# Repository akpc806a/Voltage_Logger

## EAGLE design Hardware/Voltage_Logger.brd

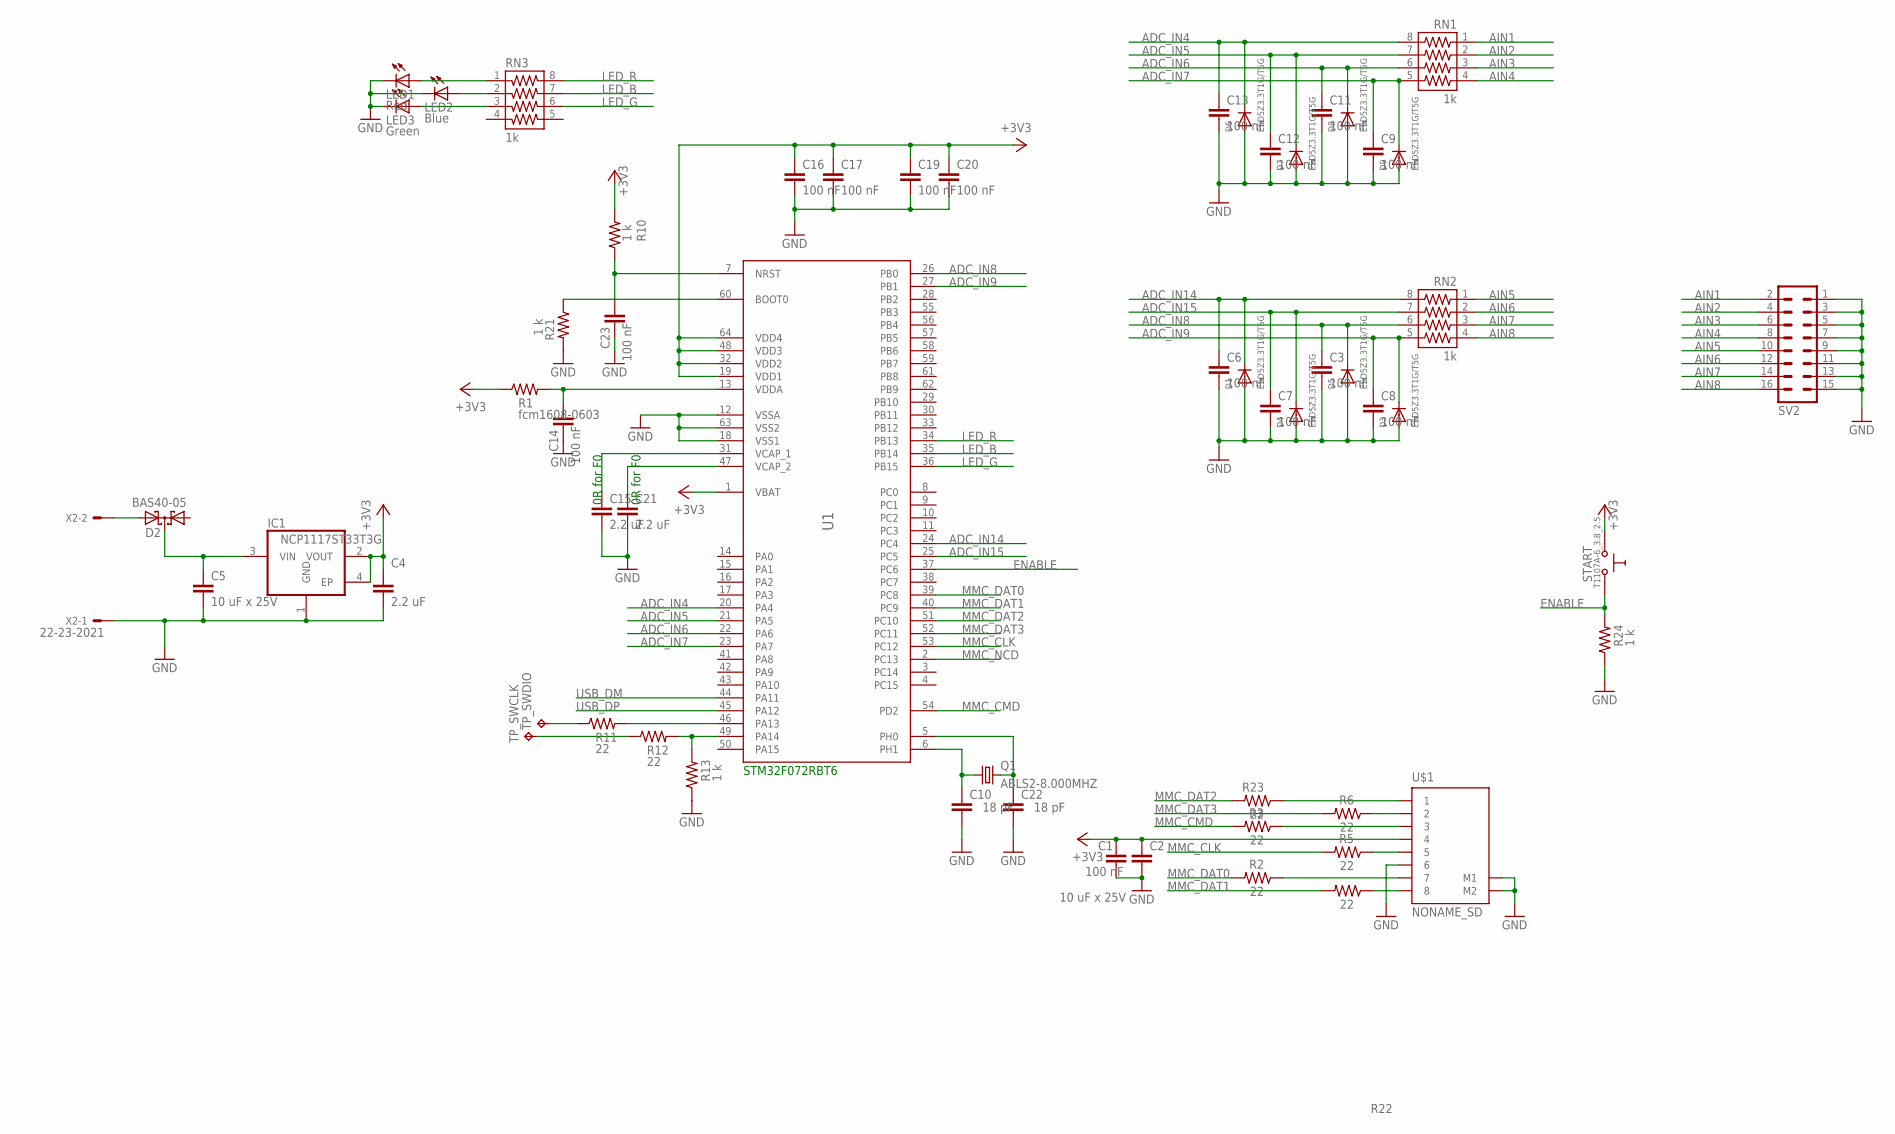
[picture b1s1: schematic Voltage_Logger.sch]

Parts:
C1, C3, C6, C7, C8, C9, C11, C12, C13, C14, C16, C17, C19, C20, C23: 100 nF; C0603
C2, C5: 10 uF x 25V; C1206
C4, C15, C21: 2.2 uF; C0603
C10, C22: 18 pF; C0603
D1, D3, D4, D5, D6, D7, D8, D9: ESD5Z3.3T1G/T5G; SOD-523
D2: BAS40-05; SOT23
IC1: NCP1117ST33T3G; SOT223
LED1: Red; LED_SML0603
LED2: Blue; LED_SML0603
LED3: Green; LED_SML0603
Q1: ABLS2-8.000MHZ; SM49
R1: fcm1608-0603; R0603
R2, R3, R5, R6, R11, R12, R22, R23: 22; R0603
R10, R13, R21, R24: 1 k; R0603
RN1, RN2, RN3: 1k; 742-8NS
START: T1107A-6_3.8_2.5; SW-TAKT_6X3.5_SMD
SV2: MA08-2
TP_SWCLK: TPTP10SQ; TP10SQ
TP_SWDIO: TPTP10SQ; TP10SQ
U1: STM32F405RGT6; LQFP64
U$1: NONAME_SD
X2: 22-23-2021

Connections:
+3V3: C1.1, C2.1, C4.1, C16.1, C17.1, C19.1, C20.1, IC1.2 (VOUT), IC1.4 (EP), R1.1, R10.2, START.P$1 (0), U1.1 (VBAT), U1.19 (VDD1), U1.32 (VDD2), U1.48 (VDD3), U1.64 (VDD4), U$1.4
ADC_IN4: C13.1, D6.K (C), RN1.8, U1.20 (PA4)
ADC_IN5: C12.1, D7.K (C), RN1.7, U1.21 (PA5)
ADC_IN6: C11.1, D8.K (C), RN1.6, U1.22 (PA6)
ADC_IN7: C9.1, D9.K (C), RN1.5, U1.23 (PA7)
ADC_IN8: C3.1, D5.K (C), RN2.6, U1.26 (PB0)
ADC_IN9: C8.1, D3.K (C), RN2.5, U1.27 (PB1)
ADC_IN14: C6.1, D1.K (C), RN2.8, U1.24 (PC4)
ADC_IN15: C7.1, D4.K (C), RN2.7, U1.25 (PC5)
AIN1: RN1.1, SV2.2
AIN2: RN1.2, SV2.4
AIN3: RN1.3, SV2.6
AIN4: RN1.4, SV2.8
AIN5: RN2.1, SV2.10
AIN6: RN2.2, SV2.12
AIN7: RN2.3, SV2.14
AIN8: RN2.4, SV2.16
ENABLE: R24.2, START.P$2 (1), U1.37 (PC6)
GND: C1.2, C2.2, C3.2, C4.2, C5.2, C6.2, C7.2, C8.2, C9.2, C10.2, C11.2, C12.2, C13.2, C14.2, C15.2, C16.2, C17.2, C19.2, C20.2, C21.2, C22.2, C23.2, D1.A, D3.A, D4.A, D5.A, D6.A, D7.A, D8.A, D9.A, IC1.1 (GND), LED1.C, LED2.C, LED3.C, R13.1, R21.2, R24.1, SV2.1, SV2.3, SV2.5, SV2.7, SV2.9, SV2.11, SV2.13, SV2.15, U1.12 (VSSA), U1.18 (VSS1), U1.63 (VSS2), U$1.6, U$1.M1, U$1.M2, X2.1
LED_B: RN3.7, U1.35 (PB14)
LED_G: RN3.6, U1.36 (PB15)
LED_R: RN3.8, U1.34 (PB13)
MMC_CLK: R5.2, U1.53 (PC12)
MMC_CMD: R3.2, U1.54 (PD2)
MMC_DAT0: R2.2, U1.39 (PC8)
MMC_DAT1: R22.2, U1.40 (PC9)
MMC_DAT2: R23.2, U1.51 (PC10)
MMC_DAT3: R6.2, U1.52 (PC11)
MMC_NCD: U1.2 (PC13)
unnamed: C15.1, U1.31 (VCAP_1)
unnamed: D2.2 (A2), X2.2
unnamed: C14.1, R1.2, U1.13 (VDDA)
unnamed: R3.1, U$1.3
unnamed: R2.1, U$1.7
unnamed: R5.1, U$1.5
unnamed: LED2.A, RN3.2
unnamed: C5.1, D2.3 (C), IC1.3 (VIN)
unnamed: R6.1, U$1.2
unnamed: LED1.A, RN3.1
unnamed: LED3.A, RN3.3
unnamed: R22.1, U$1.8
unnamed: R23.1, U$1.1
unnamed: R11.2, U1.46 (PA13)
unnamed: R12.2, R13.2, U1.49 (PA14)
unnamed: C21.1, U1.47 (VCAP_2)
unnamed: R11.1, TP_SWDIO.TP
unnamed: R12.1, TP_SWCLK.TP
unnamed: C23.1, R10.1, U1.7 (NRST)
unnamed: R21.1, U1.60 (BOOT0)
unnamed: C22.1, Q1.2, U1.5 (PH0)
unnamed: C10.1, Q1.1, U1.6 (PH1)
USB_DM: U1.44 (PA11)
USB_DP: U1.45 (PA12)

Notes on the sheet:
STM32F072RBT6
0R for F0

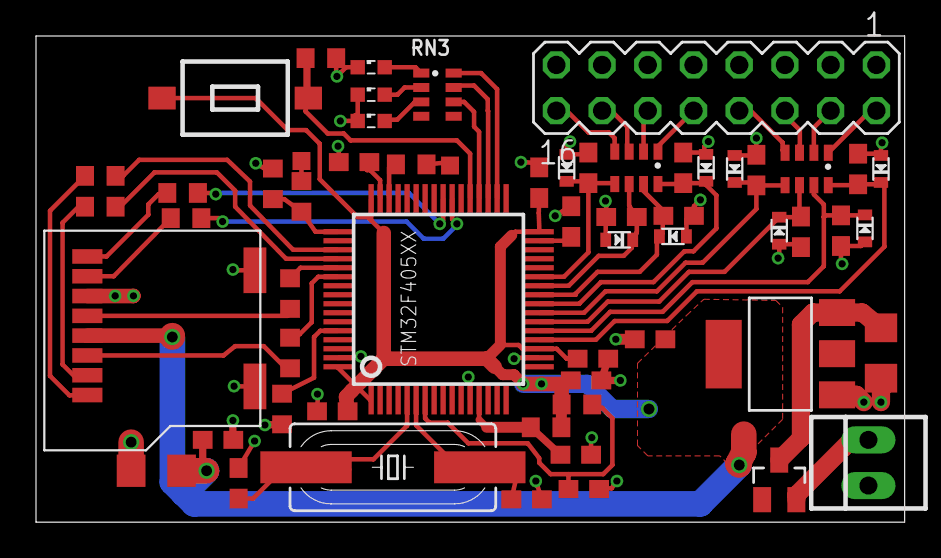
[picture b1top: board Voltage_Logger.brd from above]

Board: 2 copper layers, 48.3 x 27.0 mm, 59 parts (0 on the bottom side), 50 nets.

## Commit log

2017-02-19 initial commit of stable firmware
    (tested: sample time, channel selection, calibraion, filtering)
2017-02-19 minor code corrections
2017-02-19 hardware files added
2017-02-20 AC tests added
2017-02-22 filtering moved to ADC callback
2017-04-04 LEDs corrected
2017-04-07 channels remapped, documentation added, ready for tindie
2017-04-07 test with thermocouple added (AD8495 amplifier)
2017-04-07 temperature test updated

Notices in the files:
parts and their libraries:
resistor-array: Copyright (C) 2008, Bob Starr
microbuilder: This work is placed in the public domain, and may be freely used for commercial and non-commercial work with the following conditions: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
